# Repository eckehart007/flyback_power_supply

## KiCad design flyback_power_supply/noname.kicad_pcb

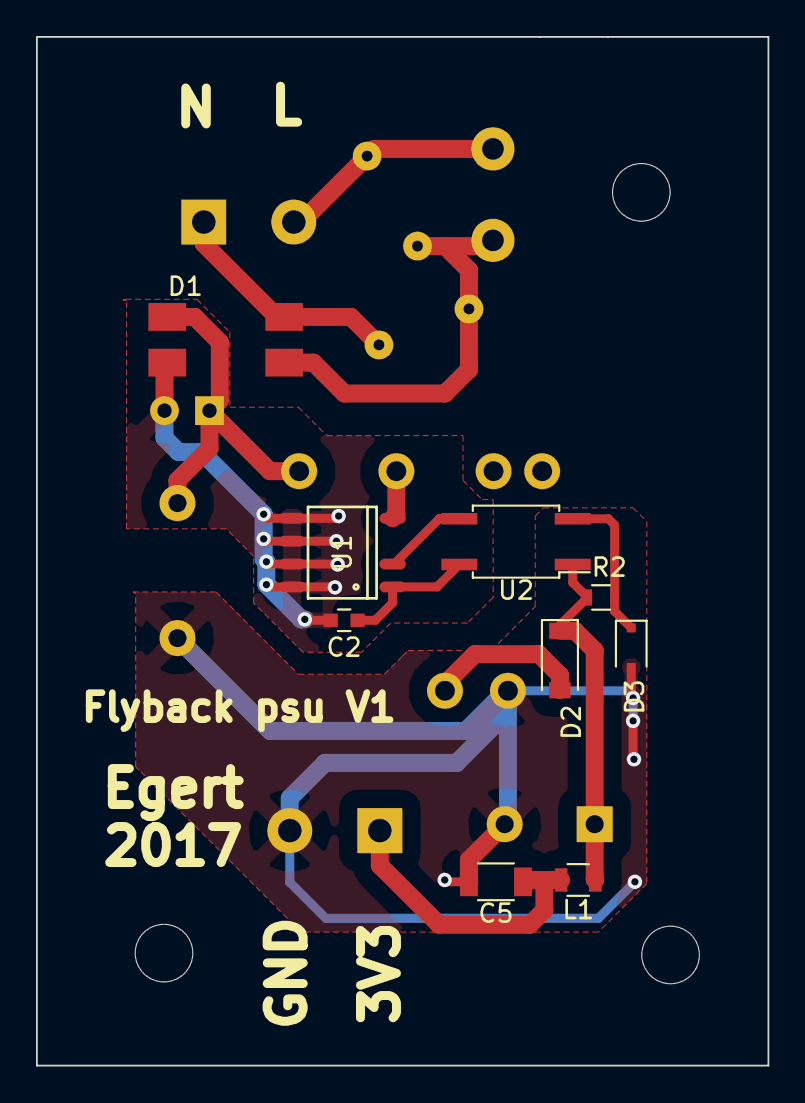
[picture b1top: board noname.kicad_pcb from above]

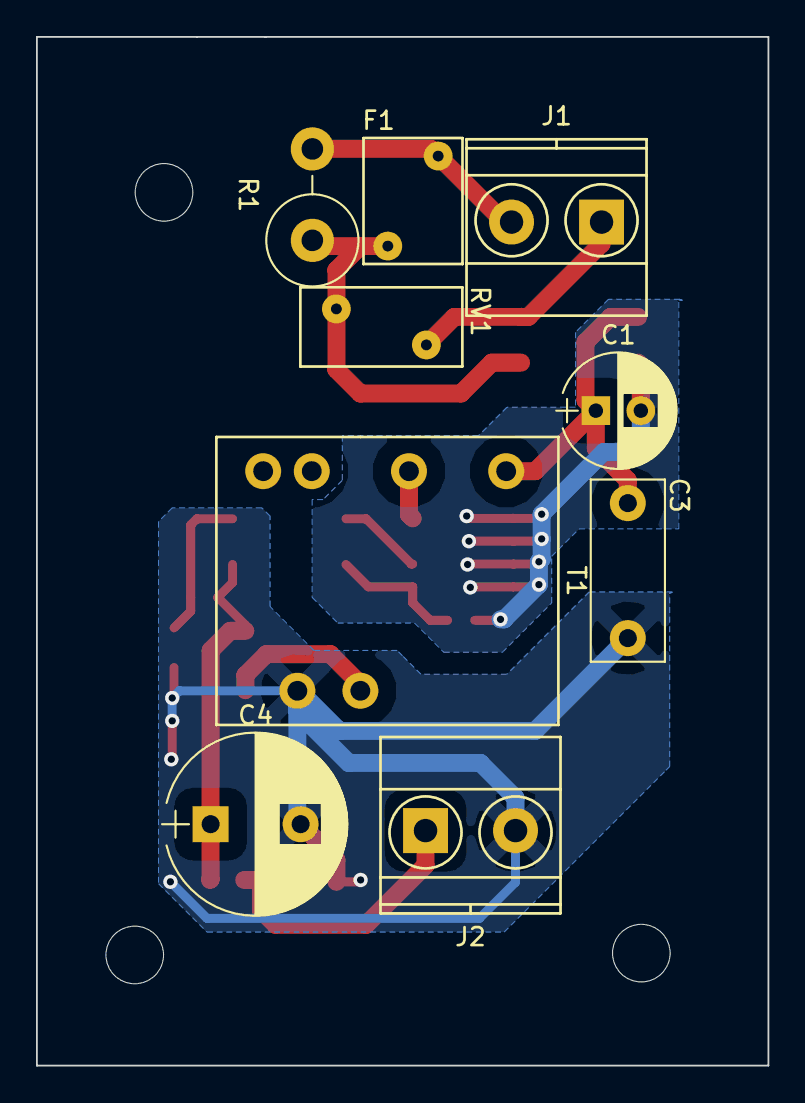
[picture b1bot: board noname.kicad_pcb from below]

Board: 2 copper layers, 40.6 x 57.2 mm, 18 parts (9 on the bottom side), 13 nets.

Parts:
C1: 2u2 / 400V; CP_Radial_D6.3mm_P2.50mm
C2: 100nF / 16V; C_0603
C3: 2n2; C_Rect_L10.0mm_W4.0mm_P7.50mm_MKS4
C4: 1000u; CP_Radial_D10.0mm_P5.00mm
C5: 100u; C_1206
D1: MB8S; SOIC-4
D2: D; D_SOD-123
D3: D_Zener; D_SOD-323F
F1: Polyfuse; RV_Disc_D7_W5.5_P5
J1, J2: CONN_01X02; TerminalBlock_Pheonix_MKDS1.5-2pol
L1: 3u3; R_0805
R1: 10R / 2W / Wirewound Resistors; R_Axial_DIN0516_L15.5mm_D5.0mm_P5.08mm_Vertical
R2: R; R_0603
RV1: Varistor, 275VAC,350DC; RV_Disc_D9_W4.4_P5
T1: FlyBckTransformer; Flybck_Transformer_M74001
U1: LNK363D; SO-8C
U2: LTV-817; SO-4_4.4x3.6mm_Pitch2.54mm

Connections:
/1: F1.2, J1.2, R1.2
/2: D1.3, F1.1, R1.1, RV1.1
/3: D1.4, J1.1, RV1.2
/5: C1.1, C3.2, D1.1, T1.6
GND: C1.2, C2.2, D1.2, U1.5, U1.6, U1.7, U1.8
GNDA: C3.1, C4.2, C5.2, D3.2, J2.2, T1.10
unnamed: C2.1, U1.1, U2.4
unnamed: C4.1, D2.1, L1.1, R2.1, U2.1
unnamed: C5.1, J2.1, L1.2
unnamed: D2.2, T1.9
unnamed: D3.1, R2.2, U2.2
unnamed: T1.4, U1.4
unnamed: U1.2, U2.3

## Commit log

2017-06-24 Init, added protection
2017-06-25 Flyback power supply
2017-08-06 Rerouted layout and added notes to front silk.
2017-08-06 Added bom
